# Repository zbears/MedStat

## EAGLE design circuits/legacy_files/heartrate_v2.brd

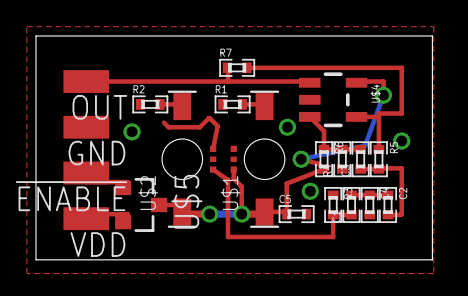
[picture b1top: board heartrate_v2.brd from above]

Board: 2 copper layers, 22.0 x 12.4 mm, 21 parts (0 on the bottom side), 12 nets.

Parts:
!ENABLE: SMD1,27-2,54
C1, C2, C4: 4.7uF; 0402
C3, C5: 2.2uF; 0402
GND: SMD1,27-2,54
OUT: SMD1,27-2,54
R1, R2: 715; 0402
R3: 12k; 0402
R4, R6: 100k; 0402
R5: 10k; 0402
R7: 3.3M; 0402
U$1, U$2: DSAH3717
U$3: APDS-9008
U$4: MCP6001; SOT23-5
U$5: P-CHANNEL-MOSFET; SOT23-3
VDD: SMD1,27-2,54

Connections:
GND: C4.2, C5.2, GND.1, R1.1, R2.1, R3.1, R4.1, U$3.GND, U$4.VSS
unnamed: R1.2, U$1.G
unnamed: U$5.2, VDD.1
unnamed: !ENABLE.1, U$5.1
unnamed: R2.2, U$2.G
unnamed: C1.1, R3.2, U$3.OUT
unnamed: C1.2, C2.1, C4.1
unnamed: C2.2, C3.1, R5.2
unnamed: C3.2, R4.2, R6.1, U$4.VIN+
unnamed: R5.1, R7.2, U$4.VIN-
OUT: OUT.1, R7.1, U$4.VOUT
VDD: C5.1, R6.2, U$1.V, U$2.V, U$3.VCC, U$4.VDD, U$5.3

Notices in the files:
parts and their libraries:
GeekAmmo: Licensing:Creative Commons ShareAlike 4.0 International - https://creativecommons.org/licenses/by-sa/4.0
